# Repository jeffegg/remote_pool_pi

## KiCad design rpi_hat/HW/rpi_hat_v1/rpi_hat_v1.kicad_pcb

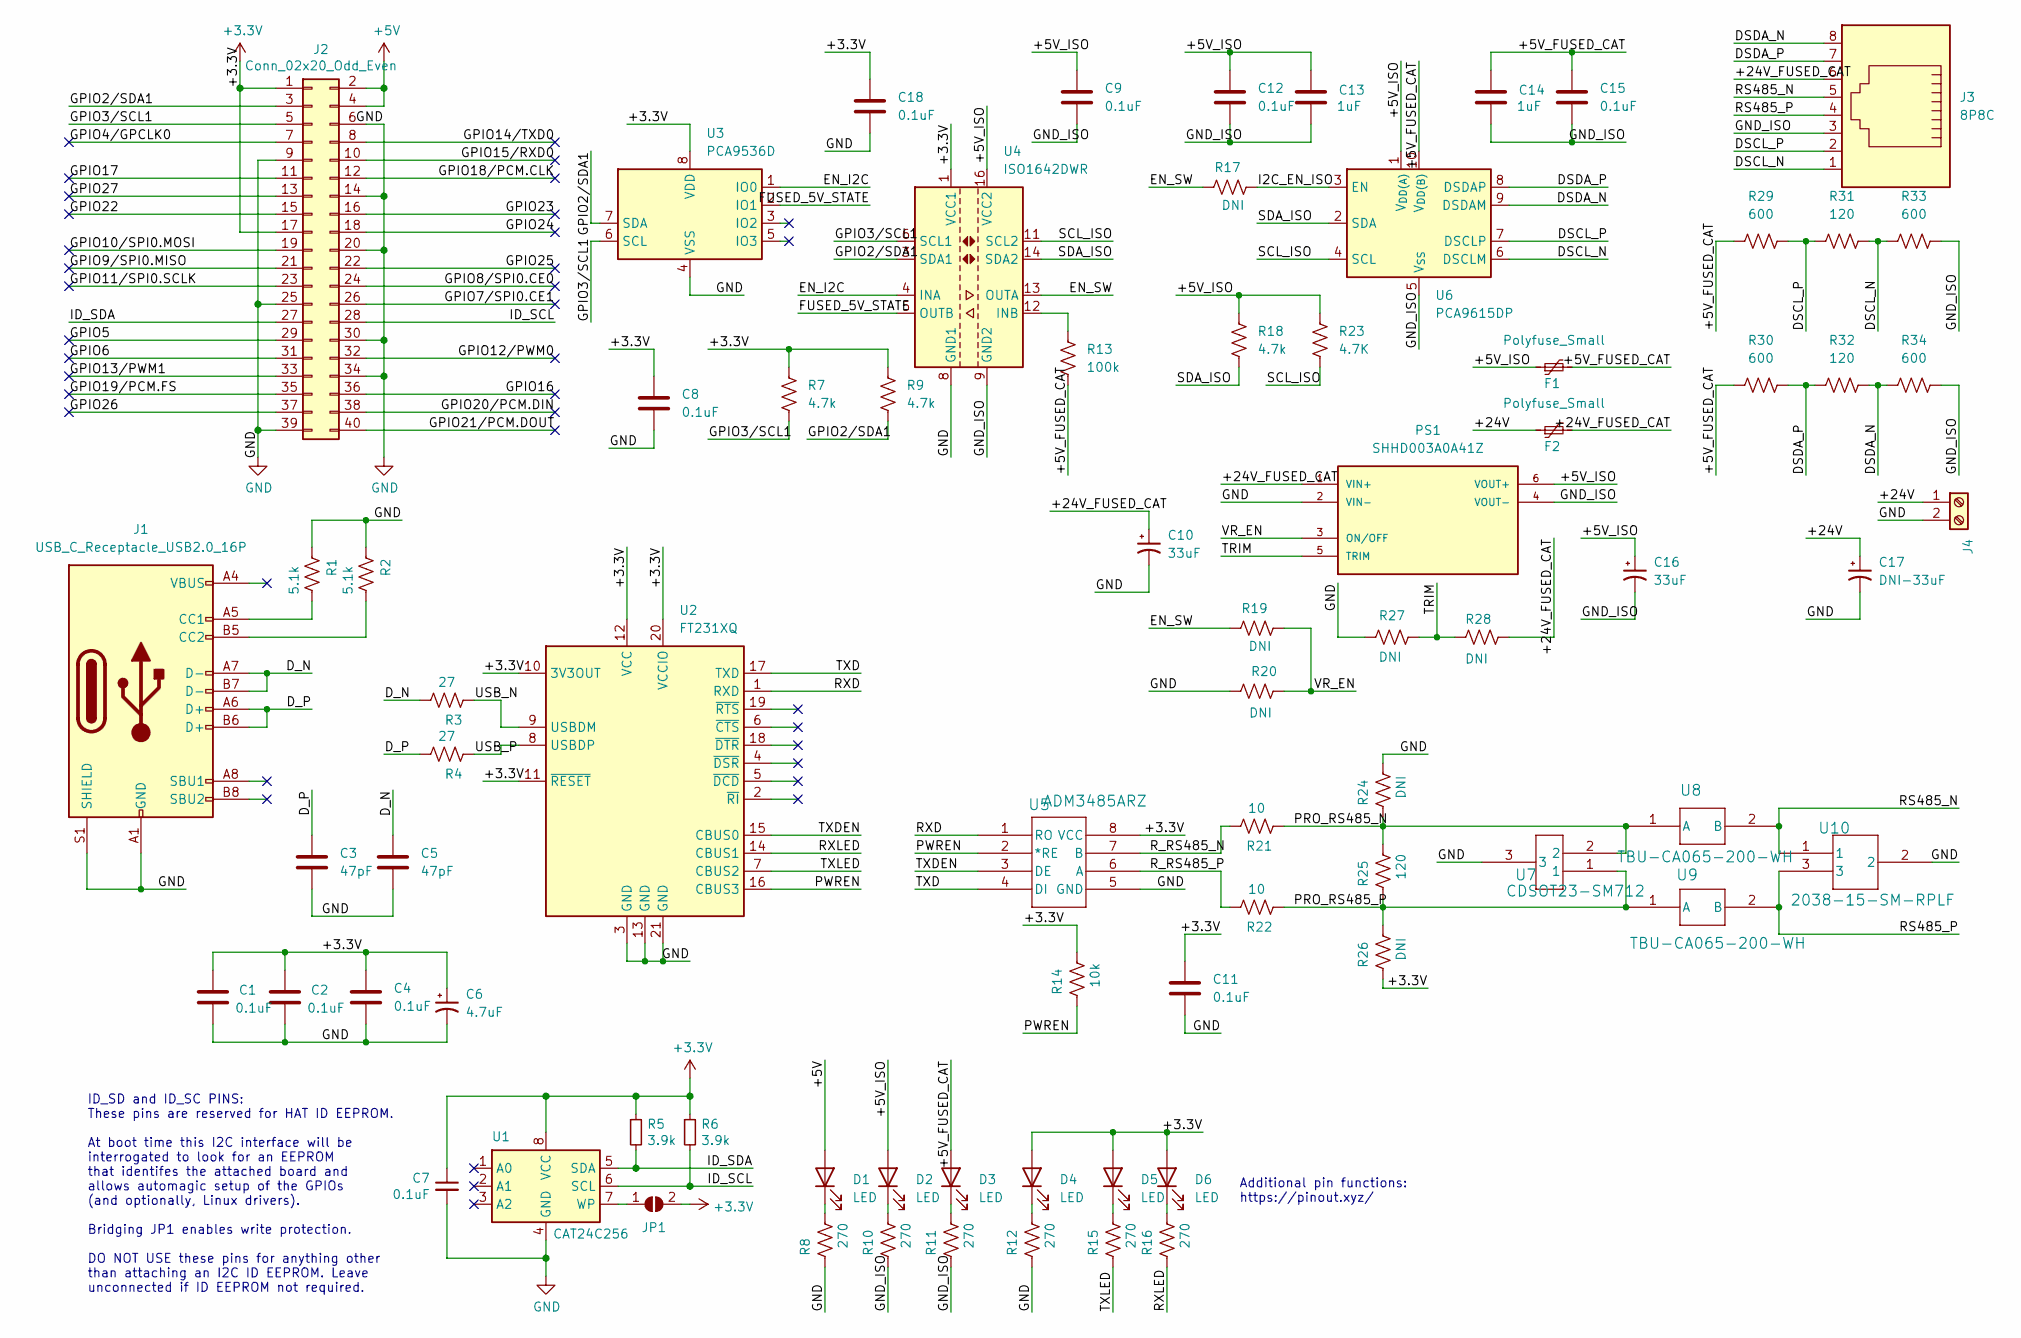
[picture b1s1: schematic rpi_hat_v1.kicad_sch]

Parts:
C1, C2, C4, C7, C8, C9, C11, C12, C15, C18: 0.1uF; C_0402_1005Metric_Pad0.74x0.62mm_HandSolder
C3, C5: 47pF; C_0402_1005Metric_Pad0.74x0.62mm_HandSolder
C6: 4.7uF; C_1206_3216Metric_Pad1.33x1.80mm_HandSolder
C10, C16: 33uF; CP_Elec_8x10
C13, C14: 1uF; C_0805_2012Metric
C17: DNI-33uF; CP_Elec_8x10
D1, D2, D3, D4, D5, D6: LED; LED_0805_2012Metric_Pad1.15x1.40mm_HandSolder
F1: Polyfuse_Small; Fuse_0805_2012Metric_Pad1.15x1.40mm_HandSolder
F2: Polyfuse_Small; Fuse_1812_4532Metric_Pad1.30x3.40mm_HandSolder
J1: USB_C_Receptacle_USB2.0_16P; USB_C_Receptacle_JAE_DX07S016JA1R1500
J2: Conn_02x20_Odd_Even; PinSocket_2x20_P2.54mm_Vertical
J3: 8P8C; CONN8_2-908LF_AMP
J4: Screw_Terminal_01x02; PinHeader_1x02_P2.54mm_Vertical
JP1: SolderJumper_2_Open; SolderJumper-2_P1.3mm_Open_Pad1.0x1.5mm
PS1: SHHD003A0A41Z; CONV_SHHD003A0A41Z
R1, R2: 5.1k; R_0402_1005Metric_Pad0.72x0.64mm_HandSolder
R3, R4: 27; R_0402_1005Metric_Pad0.72x0.64mm_HandSolder
R5, R6: 3.9k; R_0402_1005Metric_Pad0.72x0.64mm_HandSolder
R7, R9, R18: 4.7k; R_0402_1005Metric_Pad0.72x0.64mm_HandSolder
R8, R10, R11, R12, R15, R16: 270; R_0402_1005Metric_Pad0.72x0.64mm_HandSolder
R13: 100k; R_0402_1005Metric_Pad0.72x0.64mm_HandSolder
R14: 10k; R_0402_1005Metric_Pad0.72x0.64mm_HandSolder
R17, R19, R20, R24, R26, R27, R28: DNI; R_0402_1005Metric_Pad0.72x0.64mm_HandSolder
R21, R22: 10; R_0603_1608Metric_Pad0.98x0.95mm_HandSolder
R23: 4.7K; R_0402_1005Metric_Pad0.72x0.64mm_HandSolder
R25, R31, R32: 120; R_0402_1005Metric_Pad0.72x0.64mm_HandSolder
R29, R30, R33, R34: 600; R_0402_1005Metric_Pad0.72x0.64mm_HandSolder
U1: CAT24C256; SOIC-8_3.9x4.9mm_P1.27mm
U2: FT231XQ; QFN-20-1EP_4x4mm_P0.5mm_EP2.5x2.5mm
U3: PCA9536D; SOIC-8_3.9x4.9mm_P1.27mm
U4: ISO1642DWR; SOIC-16W_7.5x10.3mm_P1.27mm
U5: ADM3485ARZ; R_8_ADI
U6: PCA9615DP; TSSOP-10_3x3mm_P0.5mm
U7: CDSOT23-SM712; SOT_SM712
U8, U9: TBU-CA065-200-WH
U10: 2038-15-SM-RPLF; IC3_2038-15-SM-RPLF_BRN

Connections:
+3.3V: C1.1, C2.1, C4.1, C6.1, C7.1, C8.1, C11.1, C18.1, D4.2 (A), D5.2 (A), D6.2 (A), J2.1, J2.17, JP1.2 (B), R5.1, R6.1, R7.1, R9.1, R14.1, R26.2, U1.8 (VCC), U2.10 (3V3OUT), U2.11 (~RESET), U2.12 (VCC), U2.20 (VCCIO), U3.8 (VDD), U4.1 (VCC1), U5.8 (VCC)
+5V: D1.2 (A), J2.2, J2.4
/+5V_FUSED_CAT: C14.1, C15.1, D3.2 (A), F1.2, R13.2, R29.1, R30.1, U6.10 (V_{DD(B)})
/+5V_ISO: C9.1, C12.1, C13.1, C16.1, D2.2 (A), F1.1, PS1.6 (VOUT+), R18.1, R23.1, U4.16 (VCC2), U6.1 (V_{DD(A)})
/+24V: C17.1, F2.1, J4.1
/+24V_FUSED_CAT: C10.1, F2.2, J3.6, PS1.1 (VIN+), R28.1
/DSCL_N: J3.1, R31.2, R33.1, U6.6 (DSCLM)
/DSCL_P: J3.2, R29.2, R31.1, U6.7 (DSCLP)
/DSDA_N: J3.8, R32.2, R34.1, U6.9 (DSDAM)
/DSDA_P: J3.7, R30.2, R32.1, U6.8 (DSDAP)
/D_N: C5.1, J1.A7 (D-), J1.B7 (D-), R3.1
/D_P: C3.1, J1.A6 (D+), J1.B6 (D+), R4.1
/EN_I2C: U3.1 (IO0), U4.4 (INA)
/EN_SW: R17.2, R19.2, U4.13 (OUTA)
/FUSED_5V_STATE: U3.2 (IO1), U4.5 (OUTB)
/GND_ISO: C9.2, C12.2, C13.2, C14.2, C15.2, C16.2, J3.3, PS1.4 (VOUT-), R10.2, R11.2, R33.2, R34.2, U4.9 (GND2), U6.5 (V_{SS})
/GPIO2/SDA1: J2.3, R9.2, U3.7 (SDA), U4.3 (SDA1)
/GPIO3/SCL1: J2.5, R7.2, U3.6 (SCL), U4.6 (SCL1)
/GPIO4/GPCLK0: J2.7
/GPIO5: J2.29
/GPIO6: J2.31
/GPIO7/SPI0.CE1: J2.26
/GPIO8/SPI0.CE0: J2.24
/GPIO9/SPI0.MISO: J2.21
/GPIO10/SPI0.MOSI: J2.19
/GPIO11/SPI0.SCLK: J2.23
/GPIO12/PWM0: J2.32
/GPIO13/PWM1: J2.33
/GPIO14/TXD0: J2.8
/GPIO15/RXD0: J2.10
/GPIO16: J2.36
/GPIO17: J2.11
/GPIO18/PCM.CLK: J2.12
/GPIO19/PCM.FS: J2.35
/GPIO20/PCM.DIN: J2.38
/GPIO21/PCM.DOUT: J2.40
/GPIO22: J2.15
/GPIO23: J2.16
/GPIO24: J2.18
/GPIO25: J2.22
/GPIO26: J2.37
/GPIO27: J2.13
/I2C_EN_ISO: R17.1, U6.3 (EN)
/ID_SCL: J2.28, R6.2, U1.6 (SCL)
/ID_SDA: J2.27, R5.2, U1.5 (SDA)
/PRO_RS485_N: R21.2, R24.2, R25.1, U7.2, U8.1 (A)
/PRO_RS485_P: R22.2, R25.2, R26.1, U7.1, U9.1 (A)
/PWREN: R14.2, U2.16 (CBUS3), U5.2 (*RE)
/RS485_N: J3.5, U8.2 (B), U10.1
/RS485_P: J3.4, U9.2 (B), U10.3
/RXD: U2.1 (RXD), U5.1 (RO)
/RXLED: R16.2, U2.14 (CBUS1)
/R_RS485_N: R21.1, U5.7 (B)
/R_RS485_P: R22.1, U5.6 (A)
/SCL_ISO: R23.2, U4.11 (SCL2), U6.4 (SCL)
/SDA_ISO: R18.2, U4.14 (SDA2), U6.2 (SDA)
/TRIM: PS1.5 (TRIM), R27.1, R28.2
/TXD: U2.17 (TXD), U5.4 (DI)
/TXDEN: U2.15 (CBUS0), U5.3 (DE)
/TXLED: R15.2, U2.7 (CBUS2)
/USB_N: R3.2, U2.9 (USBDM)
/USB_P: R4.2, U2.8 (USBDP)
/VR_EN: PS1.3 (ON/OFF), R19.1, R20.1
GND: C1.2, C2.2, C3.2, C4.2, C5.2, C6.2, C7.2, C8.2, C10.2, C11.2, C17.2, C18.2, J1.A1 (GND), J1.A12 (GND), J1.B1 (GND), J1.B12 (GND), J1.S1 (SHIELD), J2.6, J2.9, J2.14, J2.20, J2.25, J2.30, J2.34, J2.39, J4.2, PS1.2 (VIN-), R1.2, R2.2, R8.2, R12.2, R20.2, R24.1, R27.2, U1.4 (GND), U2.3 (GND), U2.13 (GND), U2.21 (GND), U3.4 (VSS), U4.8 (GND1), U5.5 (GND), U7.3, U10.2
unnamed: D1.1 (K), R8.1
unnamed: D2.1 (K), R10.1
unnamed: D3.1 (K), R11.1
unnamed: D4.1 (K), R12.1
unnamed: D5.1 (K), R15.1
unnamed: D6.1 (K), R16.1
unnamed: J1.A5 (CC1), R1.1
unnamed: J1.B5 (CC2), R2.1
unnamed: JP1.1 (A), U1.7 (WP)
unnamed: R13.1, U4.12 (INB)

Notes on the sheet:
Additional pin functions: https://pinout.xyz/
ID_SD and ID_SC PINS: These pins are reserved for HAT ID EEPROM. At boot time this I2C interface will be interrogated to look for an EEPROM that identifes the attached board and allows automagic setup of the GPIOs (and optionally, Linux drivers). Bridging JP1 enables write protection. DO NOT USE th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

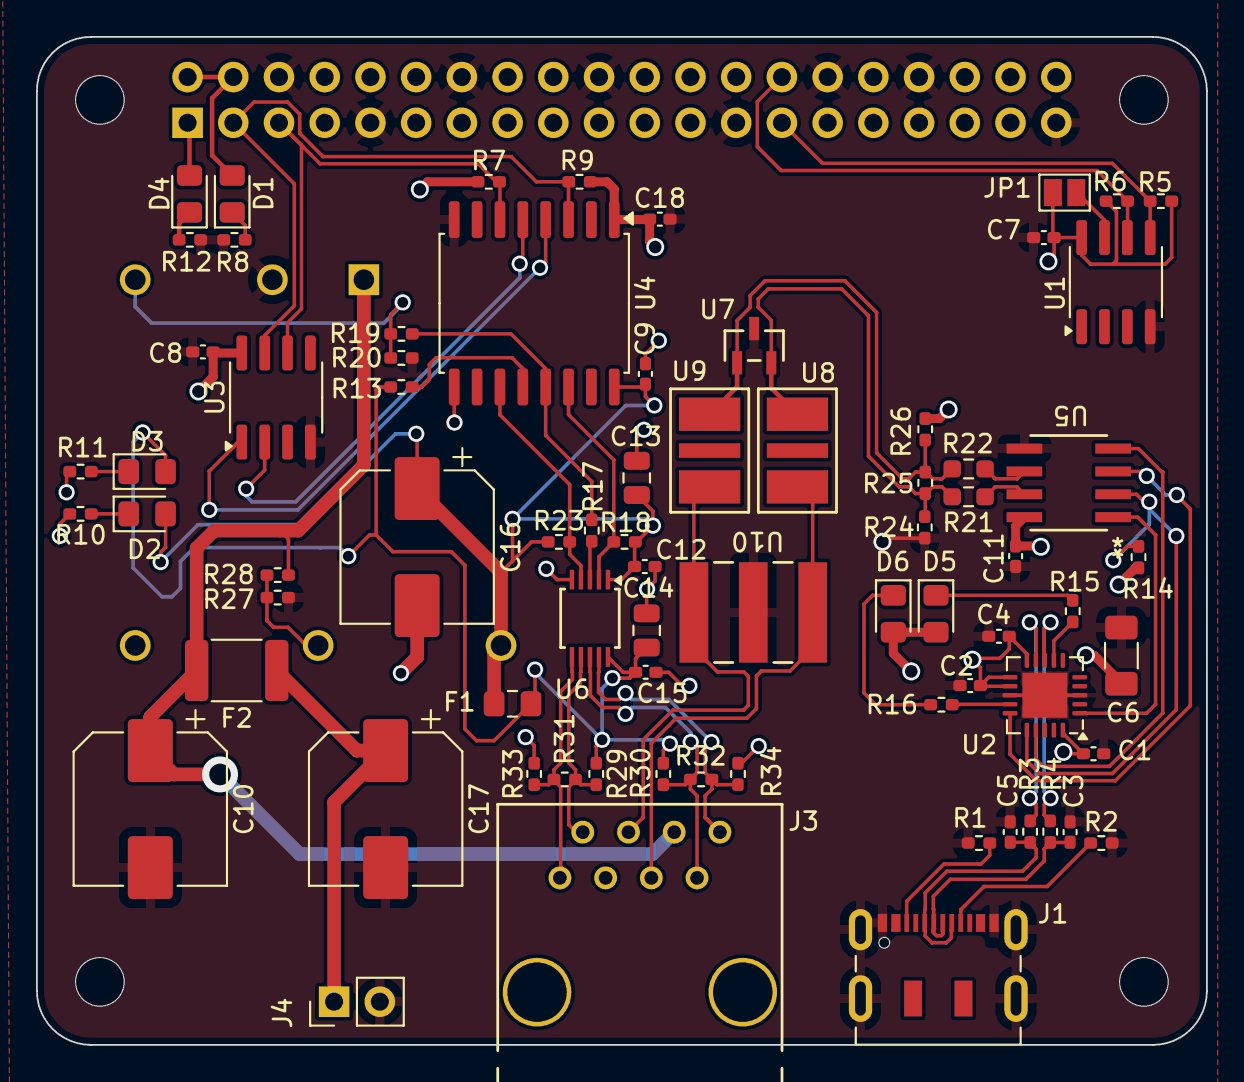
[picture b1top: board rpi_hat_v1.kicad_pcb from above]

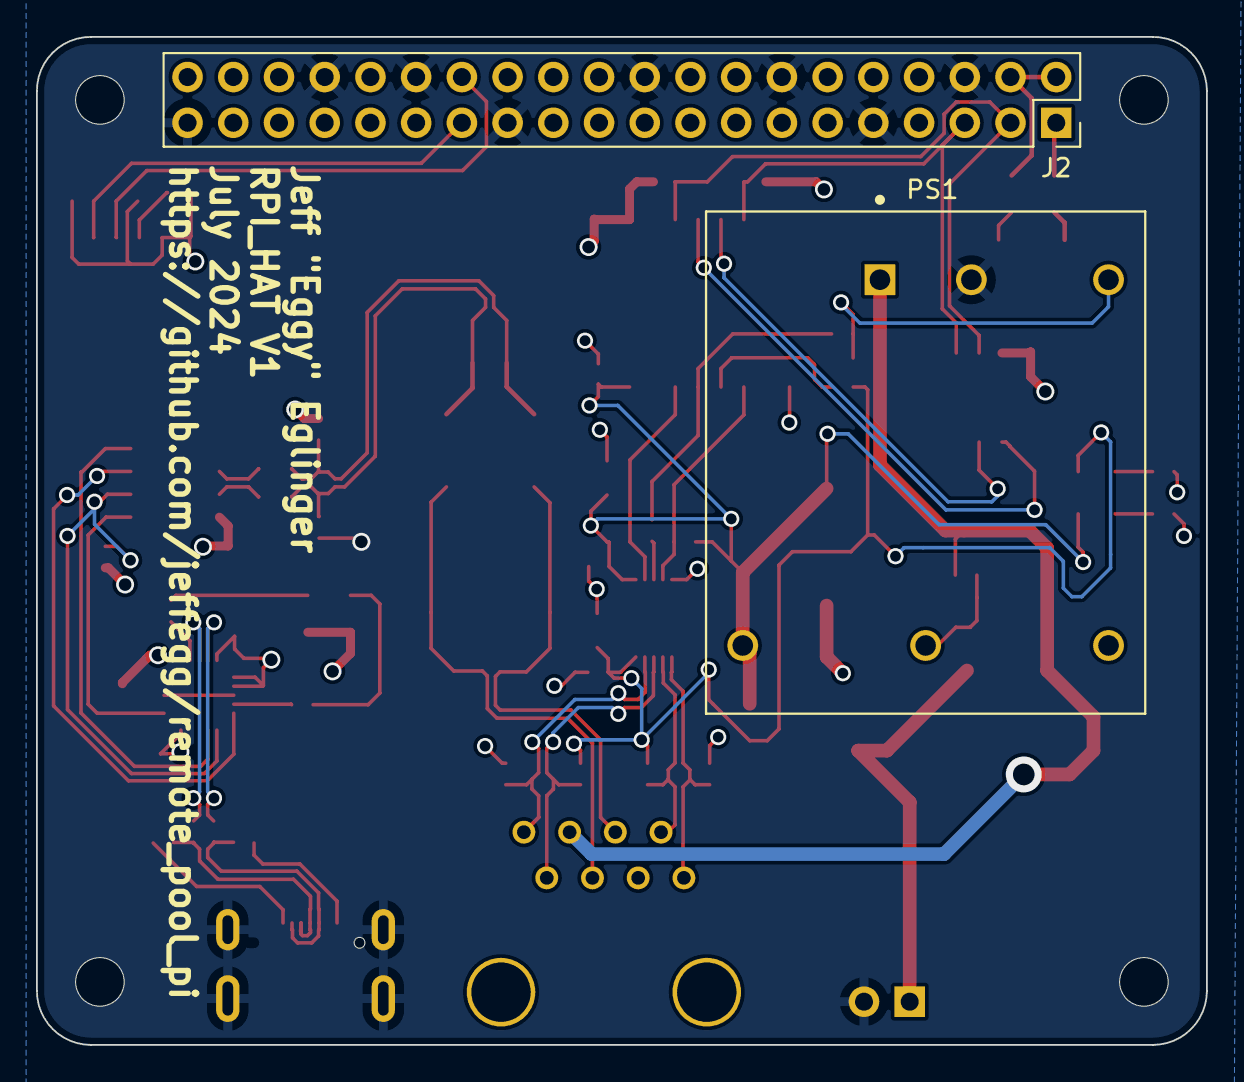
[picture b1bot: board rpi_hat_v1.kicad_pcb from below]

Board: 4 copper layers, 65.0 x 56.0 mm, 80 parts (2 on the bottom side), 50 nets.

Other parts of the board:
MH1, MH2, MH3, MH4: MountingHole_2.7mm_M2.5

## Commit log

2024-07-07 Initial Commit of RPI Hat. Complete schematics and layout. Not yet fabbed/tested.
2024-07-07 Move rpi_hat to directory for versioning. Add Remote, not finished
